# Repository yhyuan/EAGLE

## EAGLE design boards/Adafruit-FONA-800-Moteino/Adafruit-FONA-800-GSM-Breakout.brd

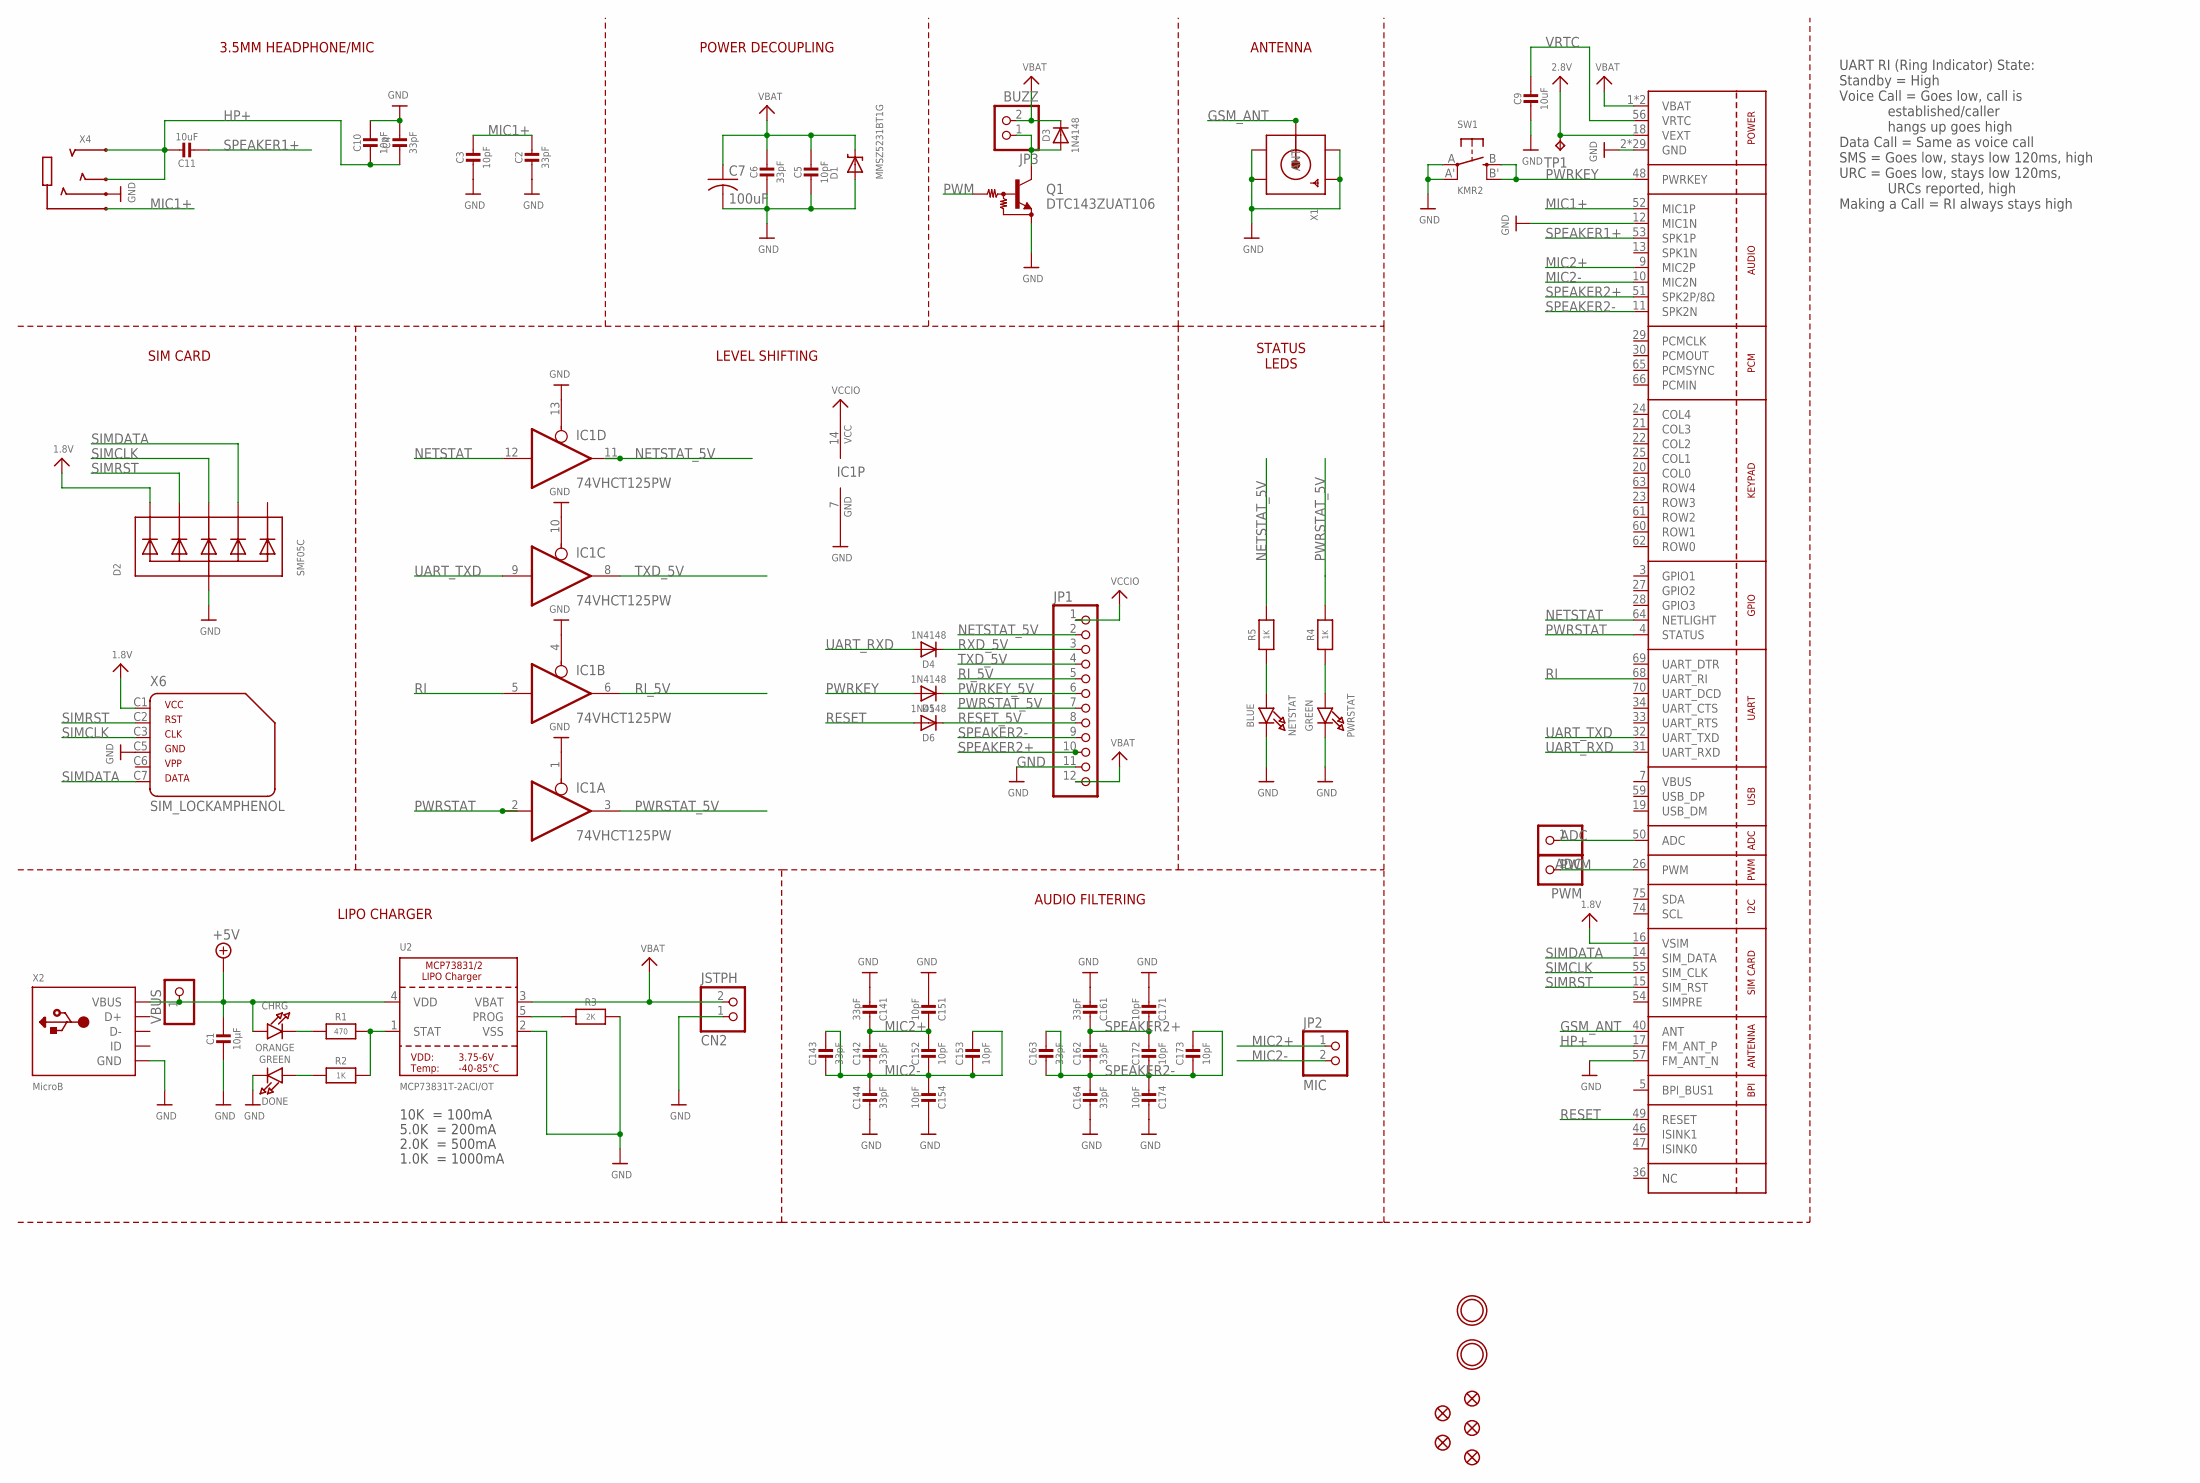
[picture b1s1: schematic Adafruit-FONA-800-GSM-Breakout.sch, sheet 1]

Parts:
ADC: PINHD-1X1CB; 1X01-CLEANBIG
C1: 10µF; 0805-NO
C2, C4, C6: 33pF; 0805-NO
C3, C5, C10: 10pF; 0805-NO
C7: 100uF; C1210
C9, C11: 10uF; 0805-NO
C14, C16: 33pF; RESPACK_4X0603
C15, C17: 10pF; RESPACK_4X0603
CHRG: ORANGE; CHIPLED_0805_NOOUTLINE
CN2: JSTPH; JSTPH2
D1: MMSZ5231BT1G; SOD-123
D2: SMF05C; SOT363
D3, D4, D5, D6: 1N4148; SOD-323
DONE: GREEN; CHIPLED_0805_NOOUTLINE
FID1, FID2, FID3, FID4, FID5: FIDUCIAL""; FIDUCIAL_1MM
IC1: 74VHCT125PW; TSSOP14
JP1: PINHD-1X12-CB; 1X12-CB
JP2: MIC; 1X02_ROUND
JP3: BUZZ; 1X02_ROUND
NETSTAT: BLUE; CHIPLED_0805_NOOUTLINE
PWM: PINHD-1X1CB; 1X01-CLEANBIG
PWRSTAT: GREEN; CHIPLED_0805_NOOUTLINE
Q1: DTC143ZUAT106; SC59-BEC
R1: 470; 0805-NO
R2, R4, R5: 1K; 0805-NO
R3: 2K; 0805-NO
SW1: KMR2; BTN_KMR2_4.6X2.8
TP1: TPTP11R; TP11R
U1: SIM800H/L; SIM800L
U2: MCP73831T-2ACI/OT; SOT23-5
U$33, U$34: MOUNTINGHOLE2.5; MOUNTINGHOLE_2.5_PLATED
VBUS: PINHD-1X1CB; 1X01-CLEANBIG
X1: SMACONNECTOR_EDGE_UFL; SMA_EDGELAUNCH_UFL
X2: MicroB; 4UCONN_20329
X4: AUDIO_3.5MMJACK_4POL; 4UCONN_18510
X6: SIM_LOCKAMPHENOL; C707_10M006_512_2

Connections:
1.8V: D2.1 (C1), U1.16 (VSIM), X6.C1 (1)
2.8V: TP1.TP, U1.18 (VEXT)
+5V: C1.1, CHRG.A, U2.4 (VDD), VBUS.1, X2.VBUS
ADC: ADC.1, U1.50 (ADC)
GND: C1.2, C2.2, C3.2, C4.1, C5.2, C6.2, C7.2, C9.2, C10.1, C14.5 (2), C14.8 (2), C15.4 (1), C15.8 (2), C16.5 (2), C16.8 (2), C17.4 (1), C17.8 (2), CN2.1, D1.A, D2.2 (A), DONE.C, IC1.1 (OE), IC1.4 (OE), IC1.7 (GND), IC1.10 (OE), IC1.13 (OE), JP1.11, NETSTAT.C, PWRSTAT.C, Q1.E, R3.2, SW1.A, SW1.A' (P1), U1.2 (GND), U1.6 (GND), U1.8 (GND), U1.12 (MIC1N), U1.35 (GND), U1.37 (GND), U1.38 (GND), U1.39 (GND), U1.41 (GND), U1.43 (GND), U1.44 (GND), U1.45 (GND), U1.57 (FM_ANT_N), U1.58 (GND), U1.67 (GND), U1.71 (GND), U1.72 (GND), U1.73 (GND), U1.76 (GND), U1.77 (GND), U1.78 (GND), U1.79 (GND), U1.80 (GND), U1.81 (GND), U1.82 (GND), U1.83 (GND), U1.84 (GND), U1.85 (GND), U1.86 (GND), U1.87 (GND), U1.88 (GND), U2.2 (VSS), X1.GND@1 (GND1), X1.GND@2 (GND2), X1.GND@3 (GND3), X1.GND@4 (GND4), X2.BASE@1 (GND), X2.BASE@2 (GND), X2.GND, X2.SPRT@1 (GND), X2.SPRT@2 (GND), X2.SPRT@3 (GND), X2.SPRT@4 (GND), X4.4-INNER_SLEEVE (RING1), X6.C5 (4); also elsewhere on the board
GSM_ANT: U1.40 (ANT), X1.P (ANT)
HP+: C4.2, C10.2, C11.1, U1.17 (FM_ANT_P), X4.2-TIP (RING3), X4.3-OUTER_SLEEVE (RING2)
MIC1+: C2.1, C3.1, U1.52 (MIC1P), X4.1-GND (TIP)
MIC2+: C14.1, C14.2 (1), C15.1, C15.2 (1), JP2.1, U1.9 (MIC2P)
MIC2-: C14.3 (1), C14.4 (1), C14.6 (2), C14.7 (2), C15.3 (1), C15.5 (2), C15.6 (2), C15.7 (2), JP2.2, U1.10 (MIC2N)
unnamed: CHRG.C, R1.1
unnamed: R1.2, R2.2, U2.1 (STAT)
unnamed: PWRSTAT.A, R4.1
unnamed: R3.1, U2.5 (PROG)
unnamed: DONE.A, R2.1
unnamed: NETSTAT.A, R5.1
unnamed: D3.A, JP3.1, Q1.C
NETSTAT: IC1.12 (I), U1.64 (NETLIGHT)
NETSTAT_5V: IC1.11 (O), JP1.2, R5.2
PWM: PWM.1, Q1.B, U1.26 (PWM)
PWRKEY: D5.A, SW1.B (S), SW1.B' (S1), U1.48 (PWRKEY)
PWRKEY_5V: D5.C, JP1.6
PWRSTAT: IC1.2 (I), U1.4 (STATUS)
PWRSTAT_5V: IC1.3 (O), JP1.7, R4.2
RESET: D6.A, U1.49 (RESET)
RESET_5V: D6.C, JP1.8
RI: IC1.5 (I), U1.68 (UART_RI)
RI_5V: IC1.6 (O), JP1.5
RXD_5V: D4.C, JP1.3
SIMCLK: D2.4 (C3), U1.55 (SIM_CLK), X6.C3 (3)
SIMDATA: D2.5 (C4), U1.14 (SIM_DATA), X6.C7 (6)
SIMRST: D2.3 (C2), U1.15 (SIM_RST), X6.C2 (2)
SPEAKER1+: C11.2, U1.53 (SPK1P)
SPEAKER2+: C16.1, C16.2 (1), C17.1, C17.2 (1), JP1.10, U1.51 (SPK2P/8Ω)
SPEAKER2-: C16.3 (1), C16.4 (1), C16.6 (2), C16.7 (2), C17.3 (1), C17.5 (2), C17.6 (2), C17.7 (2), JP1.9, U1.11 (SPK2N)
TXD_5V: IC1.8 (O), JP1.4
UART_RXD: D4.A, U1.31 (UART_RXD)
UART_TXD: IC1.9 (I), U1.32 (UART_TXD)
VBAT: C5.1, C6.1, C7.1, CN2.2, D1.C, D3.C, JP1.12, JP3.2, U1.1 (VBAT), U1.42 (VBAT), U2.3 (VBAT)
VBUS: U1.7 (VBUS)
VCCIO: IC1.14 (VCC), JP1.1
VRTC: C9.1, U1.56 (VRTC)

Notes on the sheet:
10K = 100mA
5.0K = 200mA
2.0K = 500mA
1.0K = 1000mA
UART RI (Ring Indicator) State: Standby = High Voice Call = Goes low, call is established/caller hangs up goes high Data Call = Same as voice call SMS = Goes low, stays low 120ms, high URC = Goes low, stays low 120ms, URCs reported, high Making a Call = RI always stays high
ANTENNA
POWER DECOUPLING
3.5MM HEADPHONE/MIC
SIM CARD
LEVEL SHIFTING
LIPO CHARGER
AUDIO FILTERING
STATUS LEDS

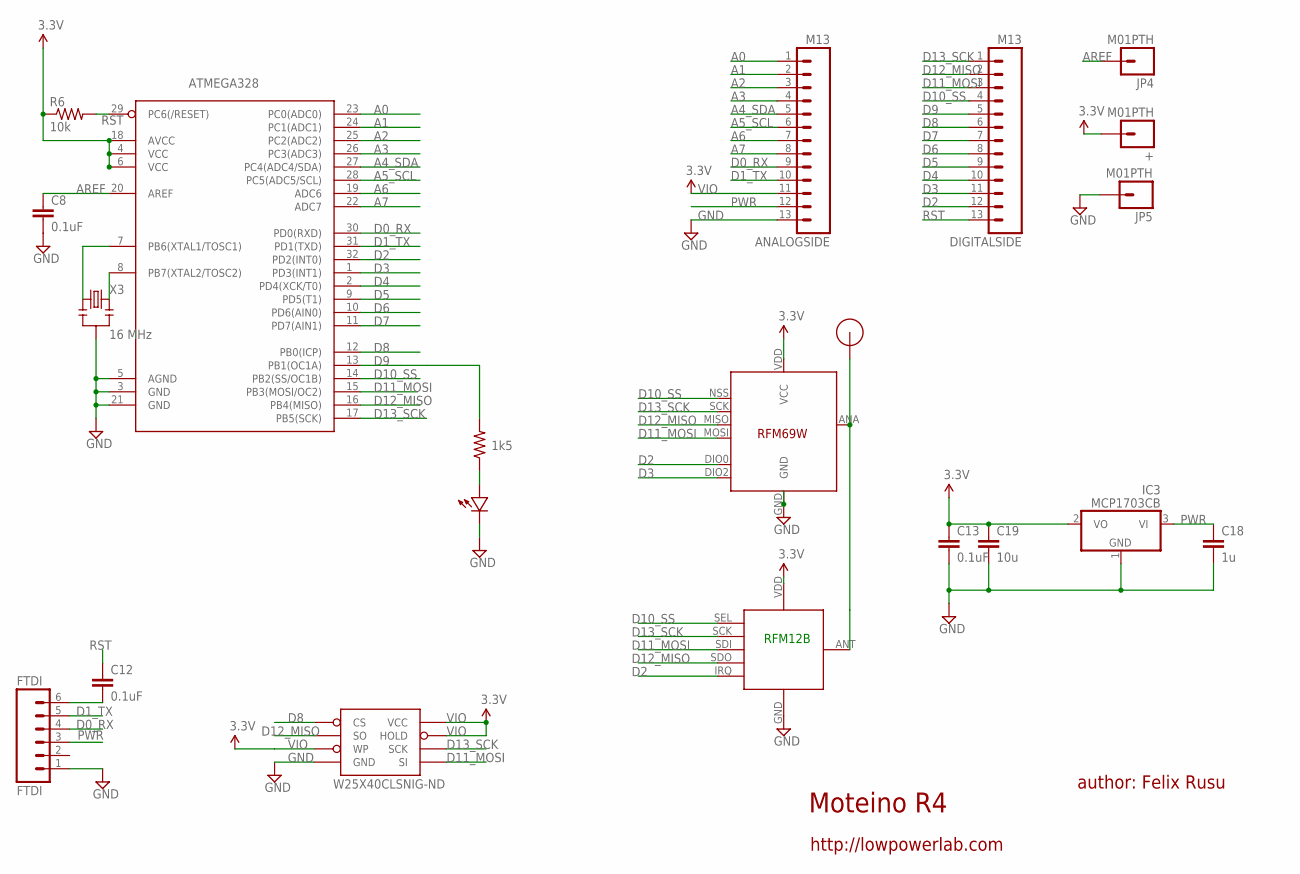
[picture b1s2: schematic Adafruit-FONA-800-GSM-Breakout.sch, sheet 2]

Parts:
+: M01PTH; 1X01
ANALOGSIDE: M13; 1X13
ATMEGA328: ATMega-328; TQFP32-08
C8, C12, C13: 0.1uF; 0603-CAP
C18: 1u; 0603-CAP
C19: 10u; 0805-CAP
DIGITALSIDE: M13; 1X13
FTDI: FTDI; 1X06
IC3: MCP1703CB; SOT23
JP4, JP5: M01PTH; 1X01
R6: 10k; 0603-RES
R7: 1k5; 0603-RES
RFM12B: RFM12B_MINPADS; RFM12B-MINPADS
U$38: LED0603; 0603-LED
U$39: RFM12B_ANTENNA; RFM12B-ANTENNA
U$42: RFM69; RFM69W-MINPADS
W25X40CLSNIG-ND: AT25F512BWIDE_5.3MM; SO08WIDE
X3: 16 MHz; RESONATOR-SMD

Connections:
A0: ANALOGSIDE.1, ATMEGA328.23 (PC0(ADC0))
A1: ANALOGSIDE.2, ATMEGA328.24 (PC1(ADC1))
A2: ANALOGSIDE.3, ATMEGA328.25 (PC2(ADC2))
A3: ANALOGSIDE.4, ATMEGA328.26 (PC3(ADC3))
A4_SDA: ANALOGSIDE.5, ATMEGA328.27 (PC4(ADC4/SDA))
A5_SCL: ANALOGSIDE.6, ATMEGA328.28 (PC5(ADC5/SCL))
A6: ANALOGSIDE.7, ATMEGA328.19 (ADC6)
A7: ANALOGSIDE.8, ATMEGA328.22 (ADC7)
AREF: ATMEGA328.20 (AREF), C8.1, JP4.1
D0_RX: ANALOGSIDE.9, ATMEGA328.30 (PD0(RXD)), FTDI.4
D1_TX: ANALOGSIDE.10, ATMEGA328.31 (PD1(TXD)), FTDI.5
D2: ATMEGA328.32 (PD2(INT0)), DIGITALSIDE.12, RFM12B.IRQ, U$42.DIO0
D3: ATMEGA328.1 (PD3(INT1)), DIGITALSIDE.11, U$42.DIO2
D4: ATMEGA328.2 (PD4(XCK/T0)), DIGITALSIDE.10
D5: ATMEGA328.9 (PD5(T1)), DIGITALSIDE.9
D6: ATMEGA328.10 (PD6(AIN0)), DIGITALSIDE.8
D7: ATMEGA328.11 (PD7(AIN1)), DIGITALSIDE.7
D8: ATMEGA328.12 (PB0(ICP)), DIGITALSIDE.6, W25X40CLSNIG-ND.1 (CS)
D9: ATMEGA328.13 (PB1(OC1A)), DIGITALSIDE.5, R7.2
D10_SS: ATMEGA328.14 (PB2(SS/OC1B)), DIGITALSIDE.4, RFM12B.SEL, U$42.NSS (SEL)
D11_MOSI: ATMEGA328.15 (PB3(MOSI/OC2)), DIGITALSIDE.3, RFM12B.SDI (SDI/MOSI), U$42.MOSI, W25X40CLSNIG-ND.5 (SI)
D12_MISO: ATMEGA328.16 (PB4(MISO)), DIGITALSIDE.2, RFM12B.SDO (SDO/MISO), U$42.MISO, W25X40CLSNIG-ND.2 (SO)
D13_SCK: ATMEGA328.17 (PB5(SCK)), DIGITALSIDE.1, RFM12B.SCK, U$42.SCK, W25X40CLSNIG-ND.6 (SCK)
GND: ANALOGSIDE.13, ATMEGA328.3 (GND), ATMEGA328.5 (AGND), ATMEGA328.21 (GND), C8.2, C13.2, C18.2, C19.2, FTDI.1, IC3.1 (GND), JP5.1, RFM12B.GND, U$38.MINUS, U$42.GND, W25X40CLSNIG-ND.4 (GND), X3.2; also elsewhere on the board
unnamed: ATMEGA328.7 (PB6(XTAL1/TOSC1)), X3.1
unnamed: R7.1, U$38.PLUS
unnamed: RFM12B.ANT, U$39.P$1, U$42.ANA (ANT)
unnamed: C12.2, FTDI.6
unnamed: ATMEGA328.8 (PB7(XTAL2/TOSC2)), X3.3
PWR: ANALOGSIDE.12, C18.1, FTDI.3, IC3.3 (VI)
RST: ATMEGA328.29 (PC6(/RESET)), C12.1, DIGITALSIDE.13, R6.2
VIO: +.1, ANALOGSIDE.11, ATMEGA328.4 (VCC), ATMEGA328.6 (VCC), ATMEGA328.18 (AVCC), C13.1, C19.1, IC3.2 (VO), R6.1, RFM12B.VDD, U$42.VDD (VCC), W25X40CLSNIG-ND.3 (WP), W25X40CLSNIG-ND.7 (HOLD), W25X40CLSNIG-ND.8 (VCC)

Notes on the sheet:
Moteino R4
author: Felix Rusu
http://lowpowerlab.com
RFM12B

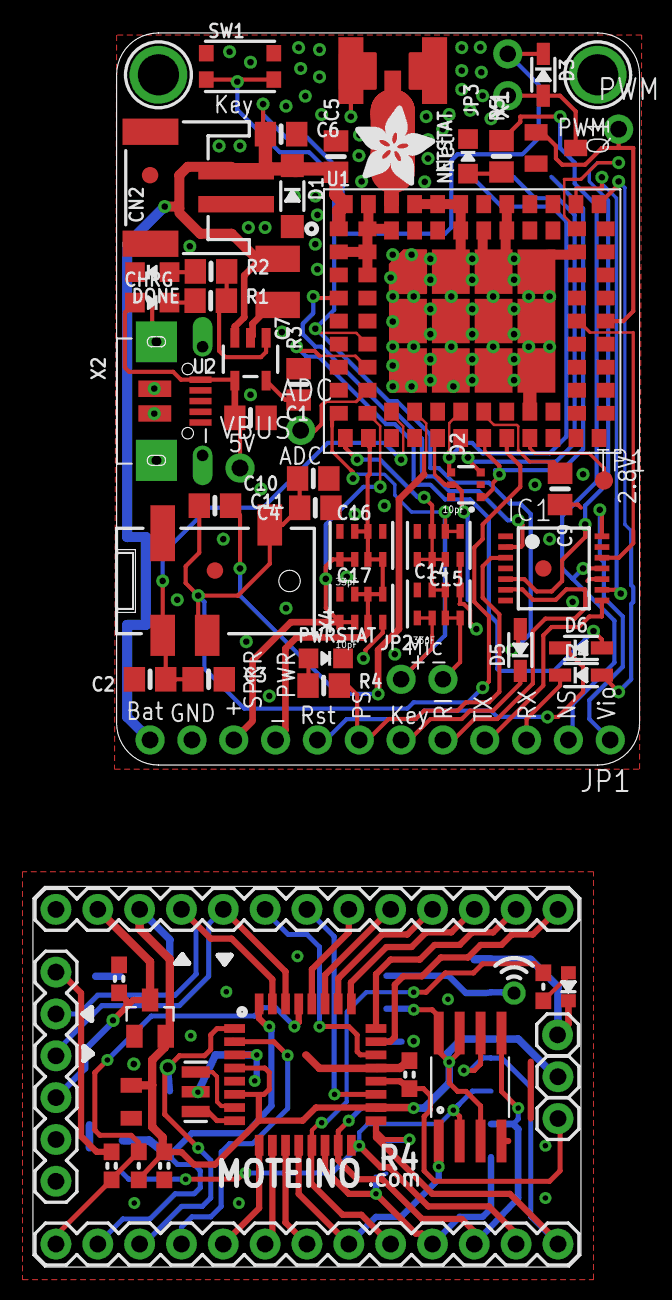
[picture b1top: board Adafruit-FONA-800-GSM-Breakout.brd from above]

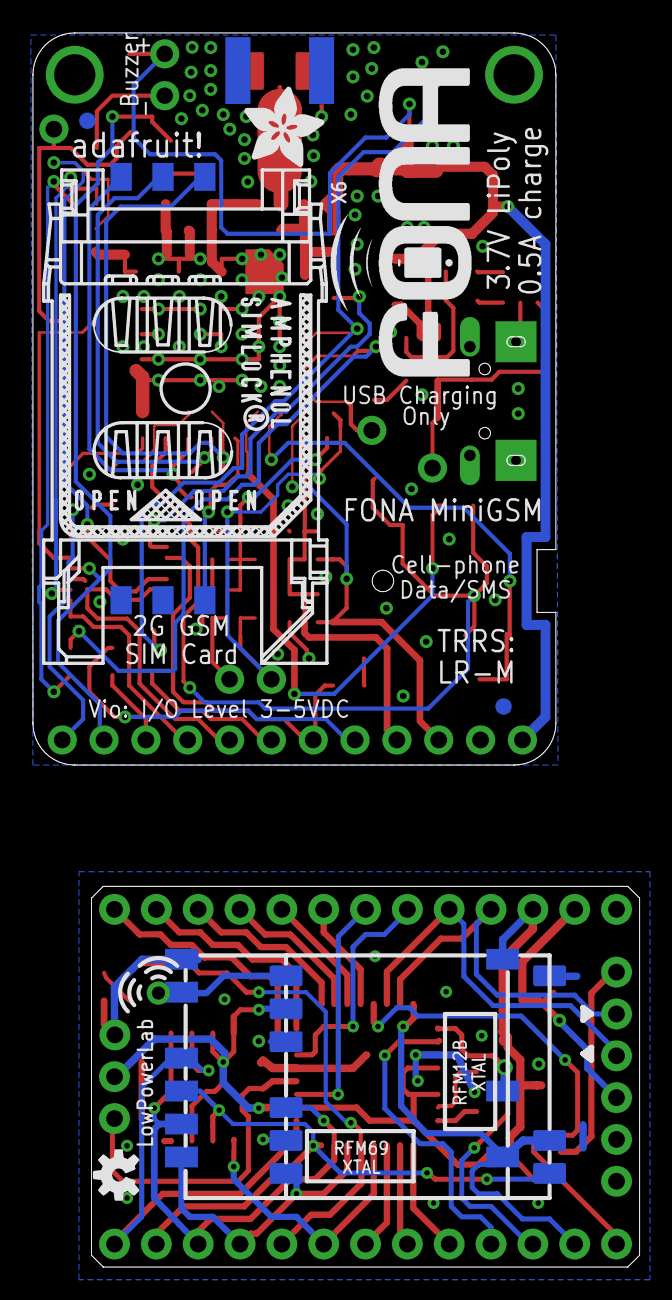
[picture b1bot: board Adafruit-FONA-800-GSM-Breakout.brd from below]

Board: 2 copper layers, 36.8 x 74.9 mm, 78 parts (8 on the bottom side), 72 nets.

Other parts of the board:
U$10, U$36: ADAFRUIT_5MM
U$26: FONA_LOGO
U$43: OSHW-LOGO-S

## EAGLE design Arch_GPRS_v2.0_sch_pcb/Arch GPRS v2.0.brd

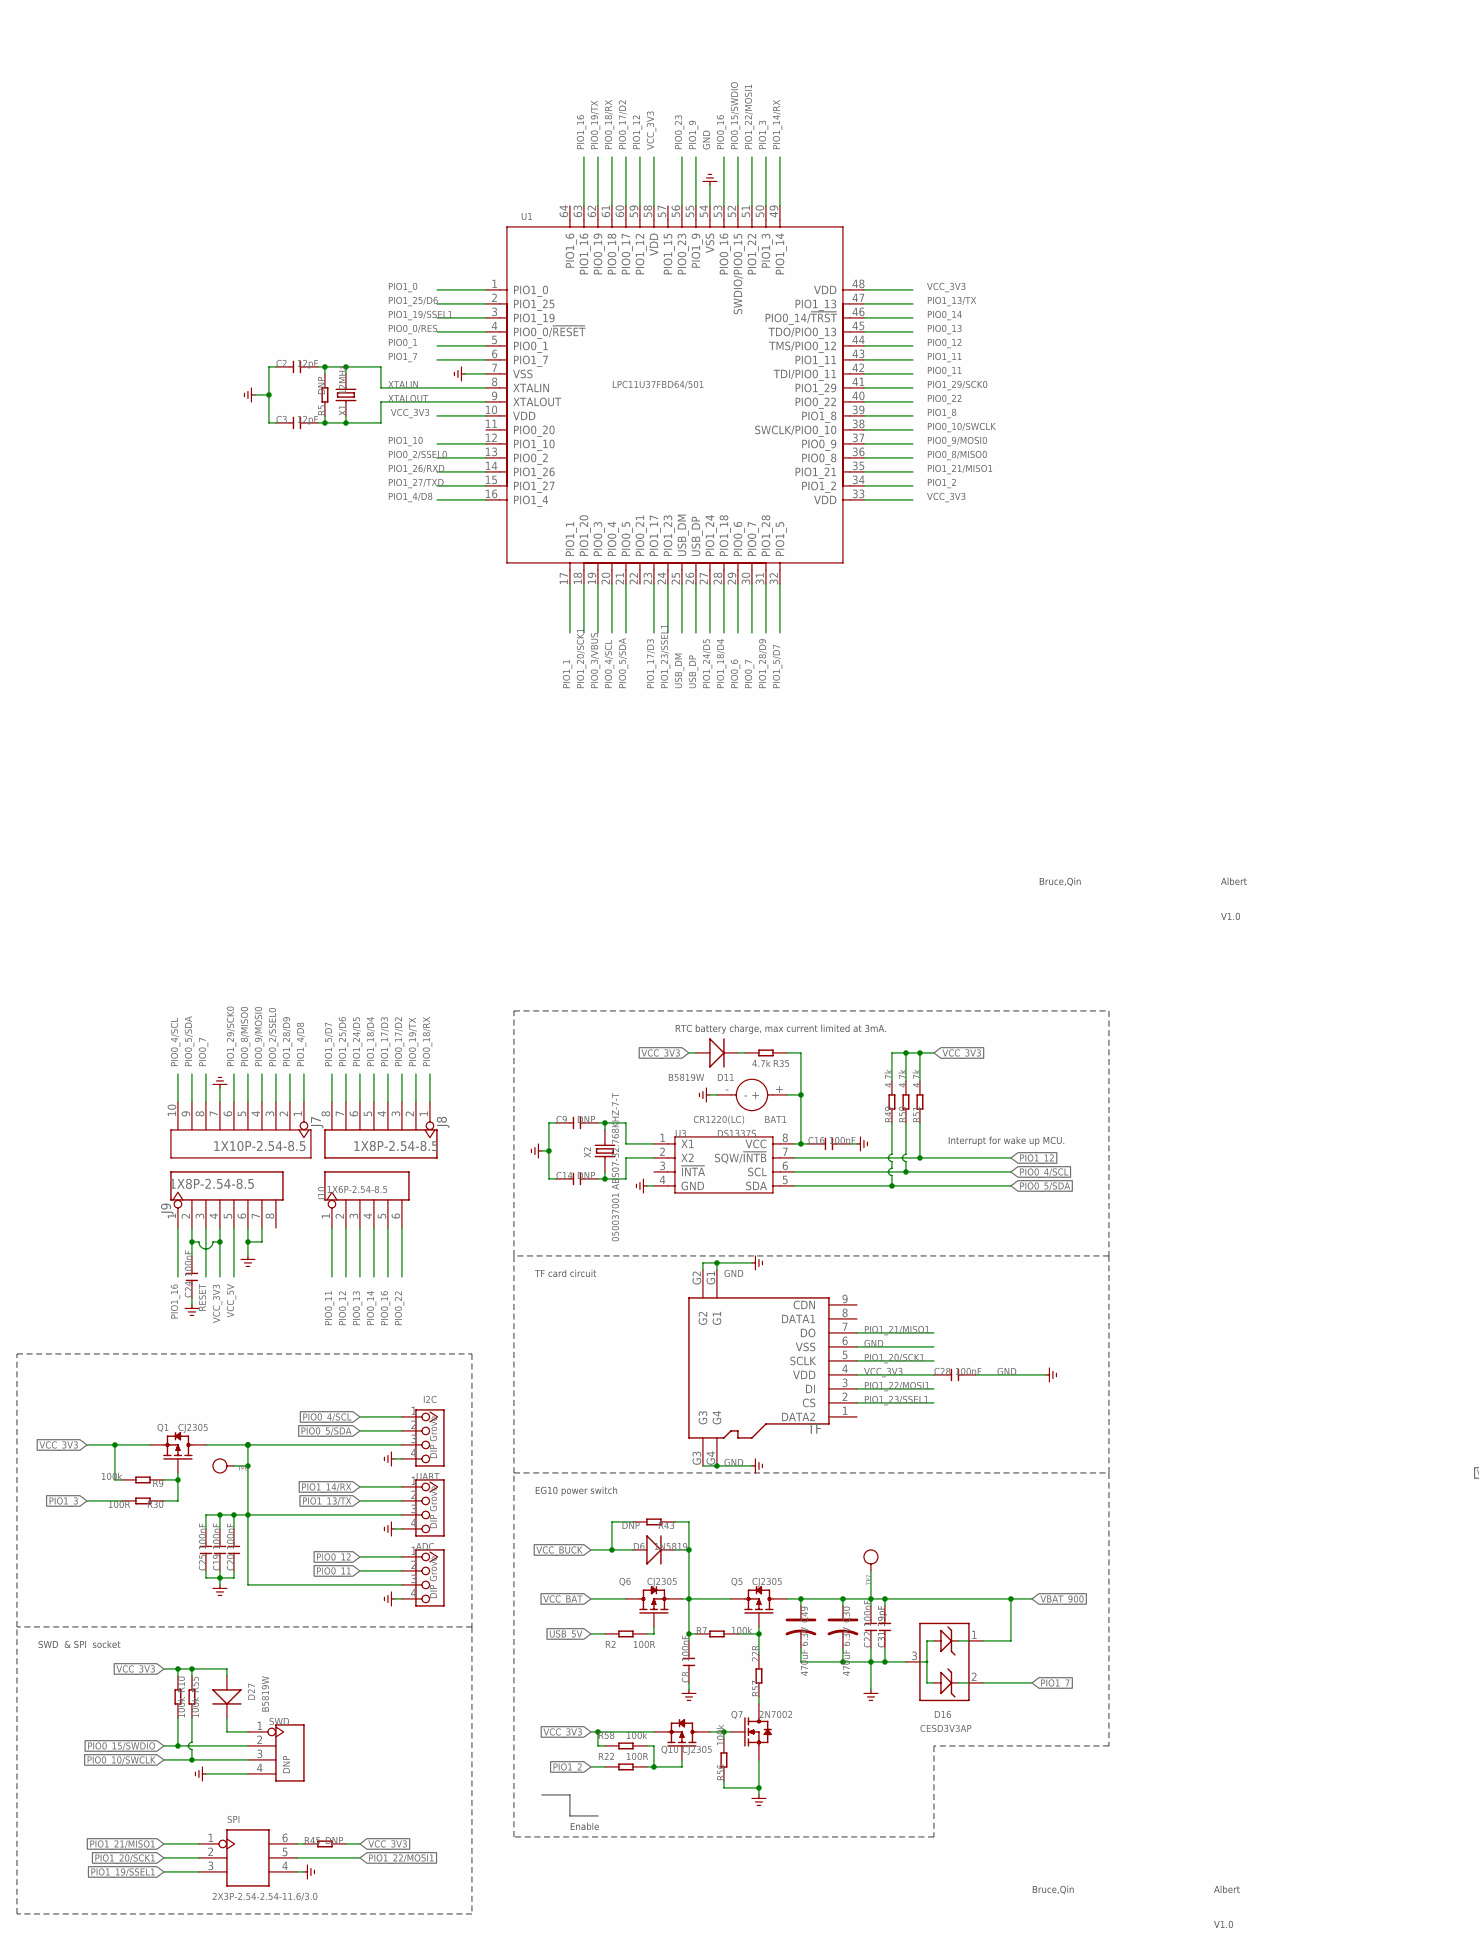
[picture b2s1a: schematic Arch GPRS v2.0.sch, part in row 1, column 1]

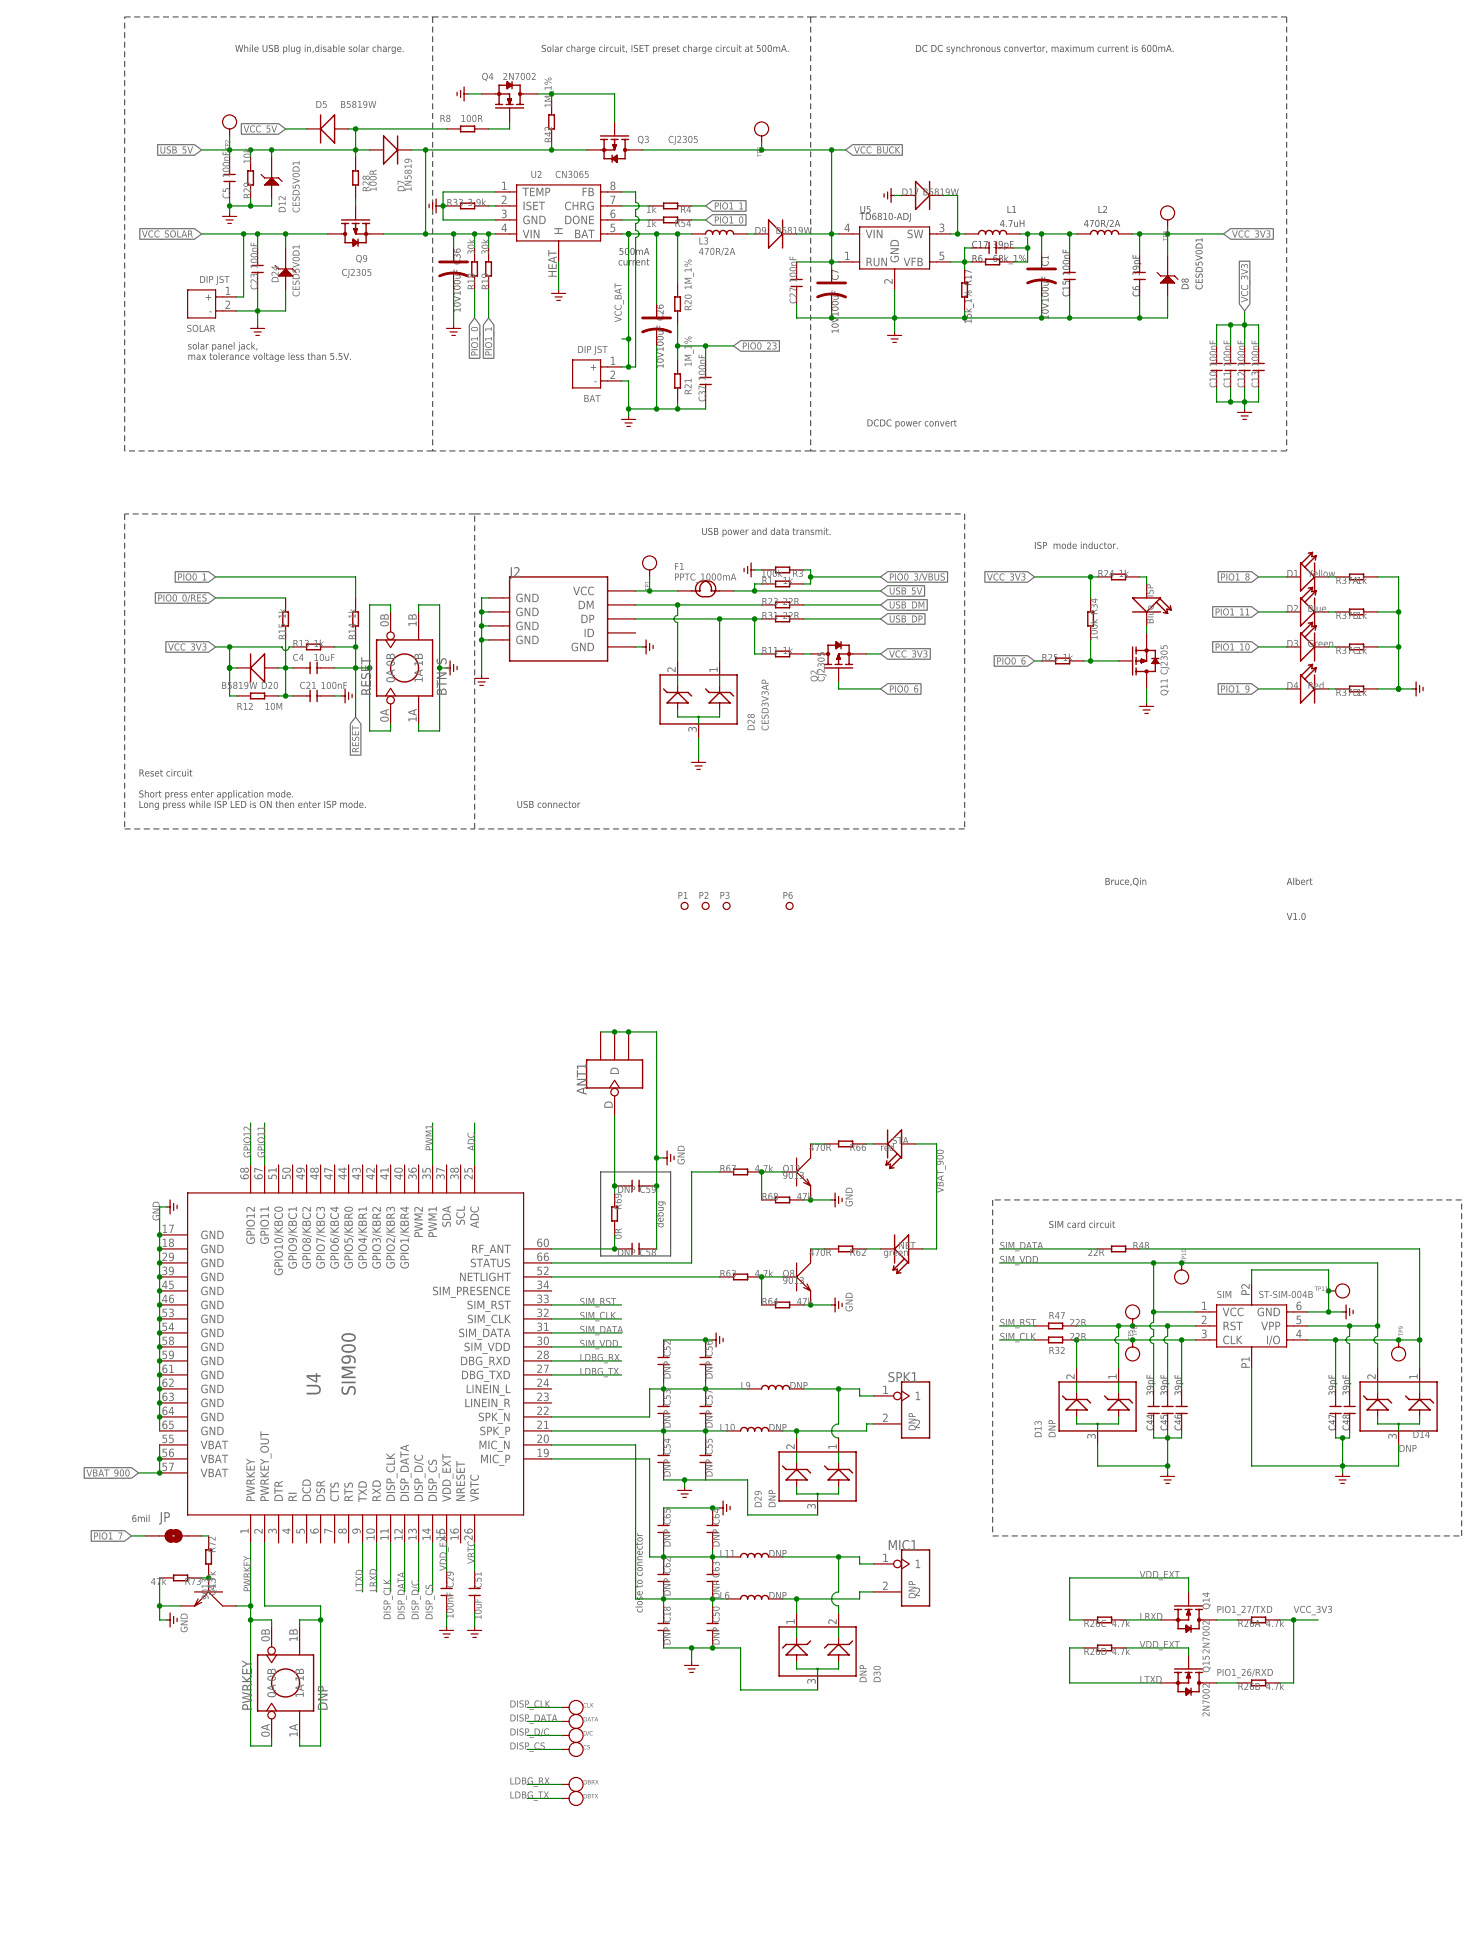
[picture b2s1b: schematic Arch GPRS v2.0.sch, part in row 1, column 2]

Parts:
ADC: DIP Grove; 4P-2.0
ANT1: ANTENNA-U-FL; 4P-U-FL
BAT: DIP JST; JST-2.0
BAT1: CR1220(LC); 2P-D12.55X2.22H
C1, C7, C26, C36: 10V100uF; AVX-B
C2, C3: 12pF; C0603
C4, C51: 10uF; C0805
C5, C8, C10, C11, C12, C13, C15, C16, C19, C20, C21, C22, C23, C24, C25, C27, C28, C29, C37: 100nF; C0603
C6, C17, C31, C44, C45, C46, C47, C48: 39pF; C0603
C9, C14, C18, C50, C52, C53, C54, C55, C56, C57, C58, C59, C62, C63, C64, C65: DNP; C0603
C30, C49: 470uF 6.3V; AVX-D
CLK: PAD-TEST-POINT-CIRCLE'4545'; TP_4545
CS: PAD-TEST-POINT-CIRCLE'4545'; TP_4545
D1: Yellow; LED-0603
D2: Blue; LED-0603
D3: Green; LED-0603
D4: Red; LED-0603
D5, D9, D11, D17, D20, D27: B5819W; SOD123
D6, D7: 1N5819; SMA
D8, D12, D24: CESD5V0D1; SOD123-2.7X1.6
D13, D14, D29, D30: DNP; SOT23
D16, D28: CESD3V3AP; SOT23
D/C: PAD-TEST-POINT-CIRCLE'4545'; TP_4545
DATA: PAD-TEST-POINT-CIRCLE'4545'; TP_4545
DBRX: DBURX; TP_4545
DBTX: PAD-TEST-POINT-CIRCLE'4545'; TP_4545
F1: PPTC_1000mA; F1206
I2C: DIP Grove; 4P-2.0
ISP: Blue; LED-0603
J2: USB-MINIUSB-5P-MICRO; MICRO-USB
J7: 1X10P-2.54-8.5; 10P-2.54
J8, J9: 1X8P-2.54-8.5; 8P-2.54
J10: 1X6P-2.54-8.5; 6P-2.54-65/35MIL
JP: PAD-SOLDERJUMPERNC; 2P-SMD-3.3X2
L1: 4.7uH; L0420
L2, L3: 470R/2A; L0805
L6, L9, L10, L11: DNP; L0603
MIC1: DNP; 2P-2.0
NET: green; LED-0603
P1, P2, P3, P6: PAD-MARK; ROUND-MARK-1.0
PWRKEY: DNP; BTN_S
Q1, Q2, Q3, Q5, Q6, Q9, Q10, Q11: CJ2305; SOT23
Q4, Q7, Q14, Q15: 2N7002; SOT23
Q8, Q12, Q13: 9013; SOT23
R1, R4, R11, R13, R14, R15, R24, R25, R54: 1k; R0603
R2, R8, R22, R28, R30: 100R; R0603
R3, R7, R9, R10, R34, R55, R56, R58: 100k; R0603
R5, R43, R45: DNP; R0603
R6: 68k_1%; R0603
R12: 10M; R0603
R17: 15k_1%; R0603
R18, R19: 30k; R0603
R20, R21, R42: 1M_1%; R0603
R23, R31, R32, R47, R48, R57: 22R; R0603
R26: 4.7k; 1206-8-3.3X2.4
R29: 10k; R0603
R33: 3.9k; R0603
R35, R49, R50, R51, R63, R67, R72: 4.7k; R0603
R37: 1k; 1206-8-3.3X2.4
R62, R66: 470R; R0603
R64, R68, R73: 47k; R0603
R69: 0R; R0603
RESET: BTN_S
SIM: ST-SIM-004B; 6P-1.8
SOLAR: DIP JST; JST-2.0
SPI: 2X3P-2.54-2.54-11.6/3.0; 2X3P-2.54
SPK1: DNP; 2P-2.0
STA: red; LED-0603
SWD: DNP; 4P-65/35MIL
TF: HOLDER-MICROSD-9P'HOLDER'; 9P-SMD-W/-RING
TP1, TP2, TP3, TP4, TP5, TP6, TP7, TP8, TP9, TP10, TP11: PAD-TEST-POINT'4545'; TP_4545
U1: LPC11U37FBD64/501; LQFP64
U2: CN3065; DFN8
U3: DS1337S; SOP8
U4: SIM900
U5: TD6810-ADJ; SOT23-5
UART: DIP Grove; 4P-2.0
X1: 12MHz; 2P-SMD-5X3.2
X2: 050037001 ABS07-32.768KHZ-7-T; 2P-SMD-3.2X1.5

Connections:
ADC: U4.25 (ADC)
DISP_CLK: CLK.T, U4.11 (DISP_CLK)
DISP_CS: CS.T, U4.14 (DISP_CS)
DISP_D/C: D/C.T, U4.13 (DISP_D/C)
DISP_DATA: DATA.T, U4.12 (DISP_DATA)
EG10_SIM_CLK: C46.2, D13.2, R32.1, SIM.3 (CLK), TP8.T
EG10_SIM_IO: C47.2, D14.1, R48.1, SIM.4 (I/O), TP9.T
EG10_SIM_RST: C45.2, D13.1, R47.1, SIM.2 (RST), TP5.T
GND: ADC.4, ANT1.GND1, ANT1.GND2, ANT1.GND3, BAT.2, BAT1.-, C1.-, C2.1, C3.1, C5.1, C6.1, C7.-, C8.1, C9.1, C10.1, C11.1, C12.1, C13.1, C14.1, C15.1, C16.2, C18.2, C19.1, C20.1, C21.1, C22.1, C23.1, C24.1, C25.1, C26.-, C27.1, C28.2, C29.2, C30.-, C31.1, C36.-, C37.1, C44.1, C45.1, C46.1, C47.1, C48.1, C49.-, C50.2, C51.1, C52.1, C54.2, C55.2, C56.1, C58.1, C59.1, C64.1, C65.1, D8.1, D12.1, D13.3, D14.3, D16.3, D17.+, D24.1, D28.3, D29.3, D30.3, I2C.4, J2.5 (GND), J2.S1 (GND), J2.S2 (GND), J2.S3 (GND), J2.S4 (GND), J2.S5 (GND), J2.S6 (GND), J7.7, J9.6, J9.7, Q4.2 (S), Q7.2 (S), Q8.2 (E), Q11.3 (D), Q12.2 (E), Q13.2 (E), R3.2, R17.2, R21.1, R29.1, R33.1, R37.5 (2), R37.6 (2), R37.7 (2), R37.8 (2), R56.1, R64.2, R68.2, R73.2, RESET.1A, RESET.1B, SIM.6 (GND), SIM.P1 (7), SIM.P2 (8), SOLAR.2, SPI.4, SWD.4, TF.6 (VSS), TF.G1, TF.G2, TF.G3, TF.G4, TP11.T, U1.7 (VSS), U1.54 (VSS), U2.1 (TEMP), U2.3 (GND), U2.HEAT (H), U3.4 (GND), U4.17 (GND), U4.18 (GND), U4.29 (GND), U4.39 (GND), U4.45 (GND), U4.46 (GND), U4.53 (GND), U4.54 (GND), U4.58 (GND), U4.59 (GND), U4.61 (GND), U4.62 (GND), U4.63 (GND), U4.64 (GND), U4.65 (GND), U5.2 (GND), UART.4
GPIO11: U4.67 (GPIO11)
GPIO12: U4.68 (GPIO12)
LDBG_RX: DBRX.T, U4.28 (DBG_RXD)
LDBG_TX: DBTX.T, U4.27 (DBG_TXD)
LRXD: Q14.2 (S), R26.3 (1), U4.10 (RXD)
LTXD: Q15.2 (S), R26.4 (1), U4.9 (TXD)
unnamed: D27.-, SWD.1
unnamed: D4.-, R37.4 (1)
unnamed: Q2.3 (D), R11.2
unnamed: Q5.1 (G), R7.2, R57.2
unnamed: R33.2, U2.2 (ISET)
unnamed: D11.-, R35.1
unnamed: C4.2, C21.2, D20.+, R12.2, R15.1
unnamed: Q3.1 (G), Q4.3 (D), R42.2
unnamed: C8.2, D6.1 (-), Q5.2 (S), Q6.2 (S), R7.1, R43.1
unnamed: D9.+, L3.2
unnamed: JP.2, R72.1
unnamed: Q1.1 (G), R9.1, R30.1
unnamed: C14.2, U3.2 (X2), X2.1
unnamed: C9.2, U3.1 (X1), X2.2
unnamed: Q11.1 (G), R25.2, R34.2
unnamed: ISP.-, Q11.2 (S)
unnamed: D3.-, R37.3 (1)
unnamed: ISP.+, R24.2
unnamed: D2.-, R37.2 (1)
unnamed: C18.1, C50.1, C62.2, C63.1, L6.1, U4.20 (MIC_N)
unnamed: R45.1, SPI.6
unnamed: BAT1.+, C16.1, R35.2, U3.8 (VCC)
unnamed: D30.1, L6.2, MIC1.2
unnamed: D30.2, L11.2, MIC1.1
unnamed: Q6.1 (G), R2.1
unnamed: D1.-, R37.1
unnamed: D17.-, L1.1, U5.3 (SW)
unnamed: D29.1, L9.2, SPK1.1
unnamed: Q9.1 (G), R28.1
unnamed: D28.2, J2.2 (DM), R23.1
unnamed: D28.1, J2.3 (DP), R11.1, R31.1
unnamed: C36.+, D7.1 (-), Q3.2 (S), Q9.2 (S), R18.2, R19.2, R42.1, U2.4 (VIN)
unnamed: F1.1, J2.1 (VCC), TP1.T
unnamed: C17.1, R6.1, R17.1, U5.5 (VFB)
unnamed: Q4.1 (G), R8.1
unnamed: R4.2, U2.7 (CHRG)
unnamed: R54.2, U2.6 (DONE)
unnamed: Q7.3 (D), R57.1
unnamed: Q7.1 (G), Q10.3 (D), R56.2
unnamed: C1.+, C15.2, C17.2, L1.2, L2.1, R6.2
unnamed: Q10.1 (G), R22.1, R58.1
unnamed: Q8.3 (C), R62.2
unnamed: NET.-, R62.1
unnamed: Q8.1 (B), R63.2, R64.1
unnamed: R63.1, U4.52 (NETLIGHT)
unnamed: C53.2, C54.1, C55.1, C57.2, L10.1, U4.21 (SPK_P)
unnamed: C52.2, C53.1, C56.2, C57.1, L9.1, U4.22 (SPK_N)
unnamed: Q12.3 (C), R66.2
unnamed: R66.1, STA.-
unnamed: Q12.1 (B), R67.2, R68.1
unnamed: R67.1, U4.66 (STATUS)
unnamed: C58.2, R69.2, U4.60 (RF_ANT)
unnamed: ANT1.D, C59.2, R69.1
unnamed: C62.1, C63.2, C64.2, C65.2, L11.1, U4.19 (MIC_P)
unnamed: Q13.1 (B), R72.2, R73.1
unnamed: PWRKEY.1A, PWRKEY.1B, U4.2 (PWRKEY_OUT)
unnamed: D29.2, L10.2, SPK1.2
PIO0_0/RES: R15.2, U1.4 (PIO0_0/!RESET)
PIO0_1: R14.2, U1.5 (PIO0_1)
PIO0_2/SSEL0: J7.3, U1.13 (PIO0_2)
PIO0_3/VBUS: R1.2, R3.1, U1.19 (PIO0_3)
PIO0_4/SCL: I2C.1, J7.10, R50.1, U1.20 (PIO0_4), U3.6 (SCL)
PIO0_5/SDA: I2C.2, J7.9, R49.1, U1.21 (PIO0_5), U3.5 (SDA)
PIO0_6: Q2.1 (G), R25.1, U1.29 (PIO0_6)
PIO0_7: J7.8, U1.30 (PIO0_7)
PIO0_8/MISO0: J7.5, U1.36 (PIO0_8)
PIO0_9/MOSI0: J7.4, U1.37 (PIO0_9)
PIO0_10/SWCLK: R55.2, SWD.3, U1.38 (SWCLK/PIO0_10)
PIO0_11: ADC.2, J10.1, U1.42 (TDI/PIO0_11)
PIO0_12: ADC.1, J10.2, U1.44 (TMS/PIO0_12)
PIO0_13: J10.3, U1.45 (TDO/PIO0_13)
PIO0_14: J10.4, U1.46 (PIO0_14/!TRST)
PIO0_15/SWDIO: R10.2, SWD.2, U1.52 (SWDIO/PIO0_15)
PIO0_16: J10.5, U1.53 (PIO0_16)
PIO0_17/D2: J8.3, U1.60 (PIO0_17)
PIO0_18/RX: J8.1, U1.61 (PIO0_18)
PIO0_19/TX: J8.2, U1.62 (PIO0_19)
PIO0_22: J10.6, U1.40 (PIO0_22)
PIO0_23: C37.2, R20.1, R21.2, U1.56 (PIO0_23)
PIO1_0: R18.1, R54.1, U1.1 (PIO1_0)
PIO1_1: R4.1, R19.1, U1.17 (PIO1_1)
PIO1_2: R22.2, U1.34 (PIO1_2)
PIO1_3: R30.2, U1.50 (PIO1_3)
PIO1_4/D8: J7.1, U1.16 (PIO1_4)
PIO1_5/D7: J8.8, U1.32 (PIO1_5)
PIO1_7: D16.2, JP.1, U1.6 (PIO1_7)
PIO1_8: D1.+, U1.39 (PIO1_8)
PIO1_9: D4.+, U1.55 (PIO1_9)
PIO1_10: D3.+, U1.12 (PIO1_10)
PIO1_11: D2.+, U1.43 (PIO1_11)
PIO1_12: R51.1, U1.59 (PIO1_12), U3.7 (SQW/!INTB)
PIO1_13/TX: U1.47 (PIO1_13), UART.2
PIO1_14/RX: U1.49 (PIO1_14), UART.1
PIO1_16: J9.1, U1.63 (PIO1_16)
PIO1_17/D3: J8.4, U1.23 (PIO1_17)
PIO1_18/D4: J8.5, U1.28 (PIO1_18)
PIO1_19/SSEL1: SPI.3, U1.3 (PIO1_19)
PIO1_20/SCK1: SPI.2, TF.5 (SCLK), U1.18 (PIO1_20)
PIO1_21/MISO1: SPI.1, TF.7 (DO), U1.35 (PIO1_21)
PIO1_22/MOSI1: SPI.5, TF.3 (DI), U1.51 (PIO1_22)
PIO1_23/SSEL1: TF.2 (CS), U1.24 (PIO1_23)
PIO1_24/D5: J8.6, U1.27 (PIO1_24)
PIO1_25/D6: J8.7, U1.2 (PIO1_25)
PIO1_26/RXD: Q15.3 (D), R26.2 (1), U1.14 (PIO1_26)
PIO1_27/TXD: Q14.3 (D), R26.1, U1.15 (PIO1_27)
PIO1_28/D9: J7.2, U1.31 (PIO1_28)
PIO1_29/SCK0: J7.6, U1.41 (PIO1_29)
PWM1: U4.35 (PWM1)
PWRKEY: PWRKEY.0A, PWRKEY.0B, Q13.3 (C), U4.1 (PWRKEY)
RESET: C4.1, J9.3, R13.2, R14.1, RESET.0A, RESET.0B
SIM_CLK: R32.2, U4.32 (SIM_CLK)
SIM_DATA: R48.2, U4.31 (SIM_DATA)
SIM_RST: R47.2, U4.33 (SIM_RST)
SIM_VDD: C44.2, C48.2, D14.2, SIM.1 (VCC), SIM.5 (VPP), TP10.T, U4.30 (SIM_VDD)
USB_5V: C5.2, D5.+, D7.2 (+), D12.2, F1.2, R1.1, R2.2, R8.2, R28.2, R29.2, TP2.T
USB_DM: R23.2, U1.25 (USB_DM)
USB_DP: R31.2, U1.26 (USB_DP)
VBAT_900: C22.2, C30.+, C31.2, C49.+, D16.1, NET.+, Q5.3 (D), STA.+, TP7.T, U4.55 (VBAT), U4.56 (VBAT), U4.57 (VBAT)
VCC_3V3: C6.2, C10.2, C11.2, C12.2, C13.2, C24.2, C28.1, D8.2, D11.+, D20.-, D27.+, J9.2, J9.4, L2.2, Q1.2 (S), Q2.2 (S), Q10.2 (S), R9.2, R10.1, R12.1, R13.1, R24.1, R26.7 (2), R26.8 (2), R34.1, R45.2, R49.2, R50.2, R51.2, R55.1, R58.2, TF.4 (VDD), TP4.T, U1.10 (VDD), U1.33 (VDD), U1.48 (VDD), U1.58 (VDD)
VCC_5V: D5.-, J9.5
VCC_BAT: BAT.1, C26.+, L3.1, Q6.3 (D), R20.2, U2.5 (BAT), U2.8 (FB)
VCC_BUCK: C7.+, C27.2, D6.2 (+), D9.-, Q3.3 (D), R43.2, TP3.T, U5.1 (RUN), U5.4 (VIN)
VCC_G: ADC.3, C19.2, C20.2, C25.2, I2C.3, Q1.3 (D), TP6.T, UART.3
VCC_SOLAR: C23.2, D24.2, Q9.3 (D), SOLAR.1
VDD_EXT: C29.1, Q14.1 (G), Q15.1 (G), R26.5 (2), R26.6 (2), U4.15 (VDD_EXT)
VRTC: C51.2, U4.26 (VRTC)
XTALIN: C2.2, R5.2, U1.8 (XTALIN), X1.2
XTALOUT: C3.2, R5.1, U1.9 (XTALOUT), X1.1

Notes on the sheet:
Bruce,Qin
Albert
V1.0
DCDC power convert
Interrupt for wake up MCU.
500mA current
While USB plug in,disable solar charge.
Solar charge circuit, ISET preset charge circuit at 500mA.
DC DC synchronous convertor, maximum current is 600mA.
solar panel jack, max tolerance voltage less than 5.5V.
USB power and data transmit.
ISP mode inductor.
RTC battery charge, max current limited at 3mA.
SIM card circuit
SWD & SPI socket
EG10 power switch
Enable
Reset circuit Short press enter application mode. Long press while ISP LED is ON then enter ISP mode.
USB connector
TF card circuit
close to connector
debug
6mil

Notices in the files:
parts and their libraries:
Aesthetics: Licensing: Creative Commons ShareAlike 4.0 International - https://creativecommons.org/licenses/by-sa/4.0
Aesthetics: Released under the Creative Commons
Aesthetics: https://creativecommons.org/licenses/by-sa/4.0
